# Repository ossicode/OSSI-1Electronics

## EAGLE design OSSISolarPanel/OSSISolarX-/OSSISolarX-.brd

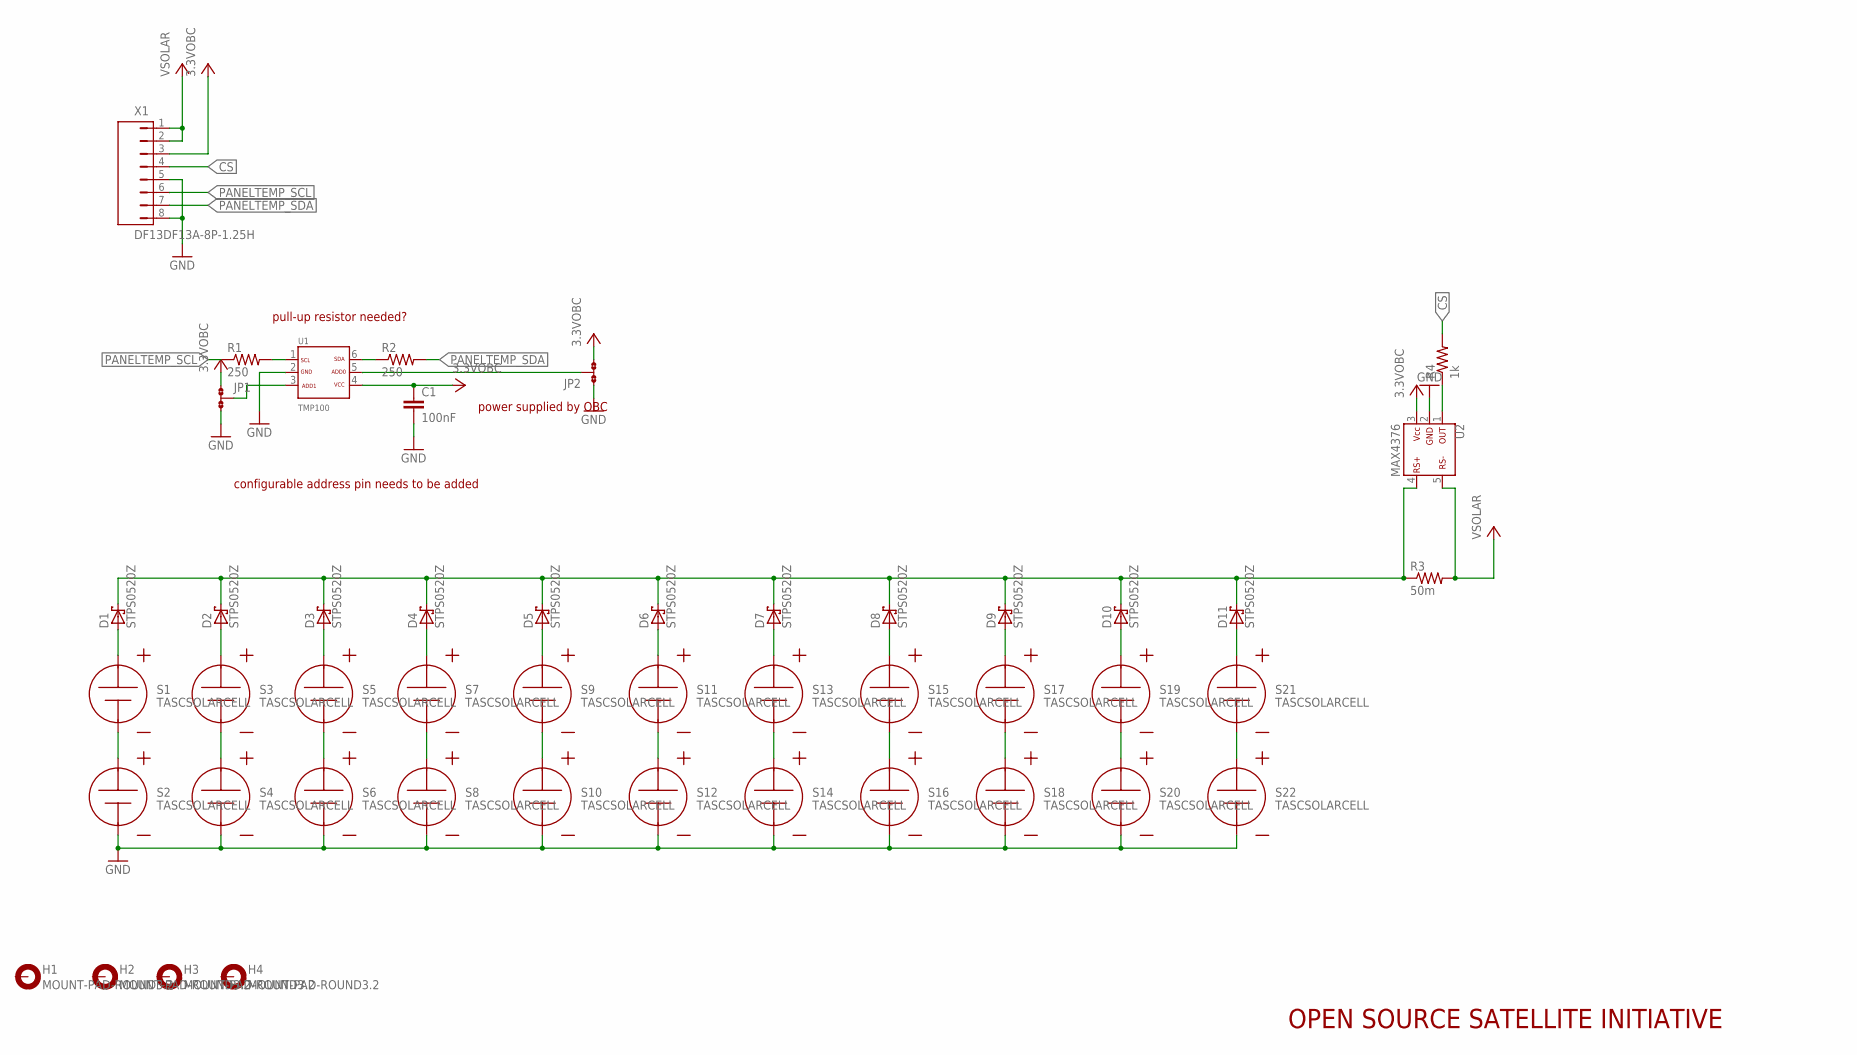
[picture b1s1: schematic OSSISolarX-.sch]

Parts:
C1: 100nF; C0603(1608)
D1, D2, D3, D4, D5, D6, D7, D8, D9, D10, D11: STPS0520Z; SOD-123
H1, H2, H3, H4: MOUNT-PAD-ROUND3.2; 3.2-PAD-ROUND
JP1, JP2: JP2; JP2SMD0603
R1, R2: 250; R0603(1608)
R3: 50m; WSL1206
R4: 1k; R0603(1608)
S1, S2, S3, S4, S5, S6, S7, S8, S9, S10, S11, S12, S13, S14, S15, S16, S17, S18, S19, S20, S21, S22: TASCSOLARCELL
U1: TMP100; SOT23-6DBV
U2: MAX4376; SOT23-5DBV
X1: DF13DF13A-8P-1.25H; DF13A-8P

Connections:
3.3VOBC: C1.1, JP1.1, JP2.3, U1.4, U2.3, X1.3
CS: R4.2, X1.4
GND: C1.2, JP1.3, JP2.1, S2.N, S4.N, S6.N, S8.N, S10.N, S12.N, S14.N, S16.N, S18.N, S20.N, S22.N, U1.2, U2.2, X1.5, X1.8
unnamed: S1.N, S2.P
unnamed: D1.A, S1.P
unnamed: S3.N, S4.P
unnamed: D2.A, S3.P
unnamed: S5.N, S6.P
unnamed: D3.A, S5.P
unnamed: S7.N, S8.P
unnamed: D4.A, S7.P
unnamed: S9.N, S10.P
unnamed: D5.A, S9.P
unnamed: S11.N, S12.P
unnamed: D6.A, S11.P
unnamed: S13.N, S14.P
unnamed: D7.A, S13.P
unnamed: S15.N, S16.P
unnamed: D8.A, S15.P
unnamed: S17.N, S18.P
unnamed: D9.A, S17.P
unnamed: S19.N, S20.P
unnamed: D10.A, S19.P
unnamed: S21.N, S22.P
unnamed: D11.A, S21.P
unnamed: R1.2, U1.1
unnamed: R2.1, U1.6
unnamed: D1.C, D2.C, D3.C, D4.C, D5.C, D6.C, D7.C, D8.C, D9.C, D10.C, D11.C, R3.P$1 (1), U2.4
unnamed: JP1.2, U1.3
unnamed: JP2.2, U1.5
unnamed: R4.1, U2.1
PANELTEMP_SCL: R1.1, X1.6
PANELTEMP_SDA: R2.2, X1.7
VSOLAR: R3.P$2 (2), U2.5, X1.1, X1.2

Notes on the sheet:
configurable address pin needs to be added
pull-up resistor needed?
power supplied by OBC
OPEN SOURCE SATELLITE INITIATIVE

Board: 2 copper layers, 47 parts (0 on the bottom side), 34 nets, no tracks yet.

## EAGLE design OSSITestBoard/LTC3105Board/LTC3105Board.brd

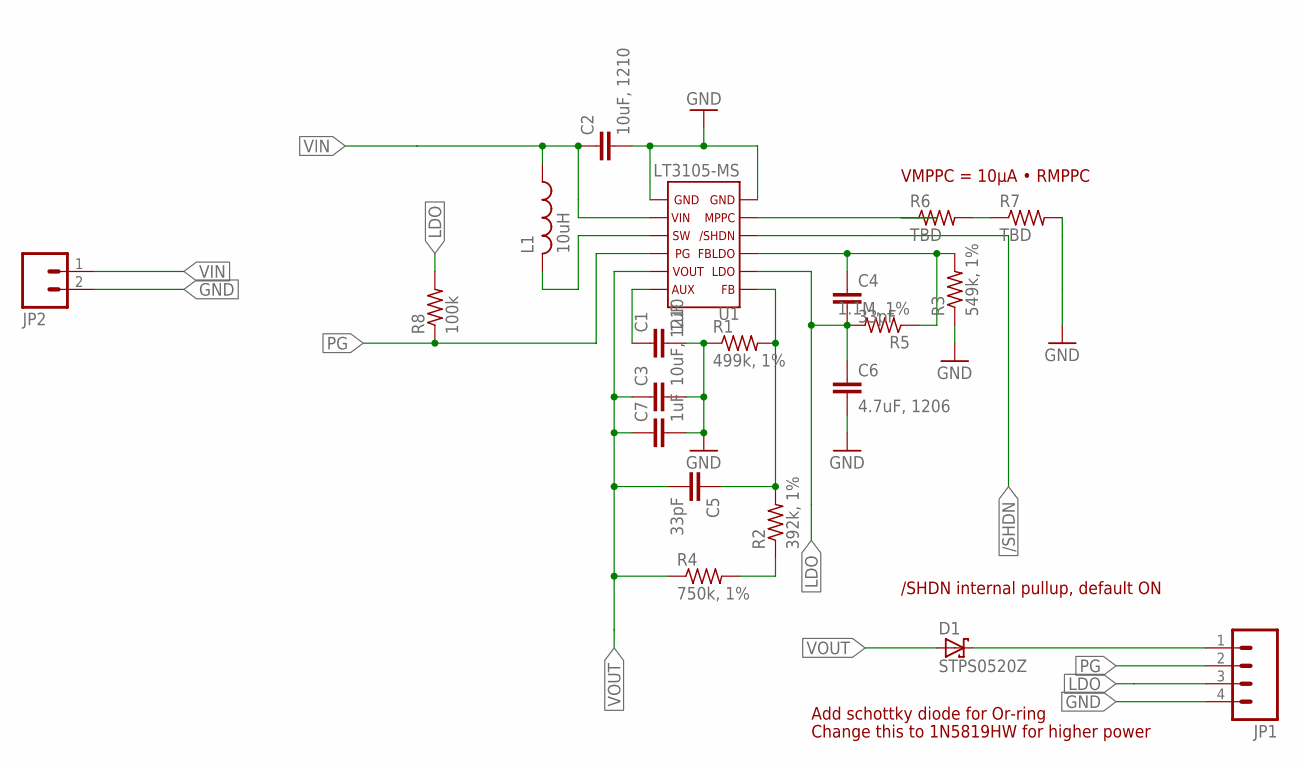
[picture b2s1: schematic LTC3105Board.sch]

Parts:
C1, C7: 1uF; C0603(1608)
C2, C3: 10uF, 1210; C1210-GCM32
C4, C5: 33pF; C0603(1608)
C6: 4.7uF, 1206; C1206-GCM31
D1: STPS0520Z; SOD-123
JP1: M04PTH; 1X04
JP2: M02PTH; 1X02
L1: 10uH; CDRH3D18
R1: 499k, 1%; R0603(1608)
R2: 392k, 1%; R0603(1608)
R3: 549k, 1%; R0603(1608)
R4: 750k, 1%; R0603(1608)
R5: 1.1M, 1%; R0603(1608)
R6, R7: TBD; R0603(1608)
R8: 100k; R0603(1608)
U1: LT3105-MS; MSOP-12-MS

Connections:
/SHDN: U1.4
GND: C1.2, C2.P$2 (2), C3.P$2 (2), C6.P$2 (2), C7.2, JP1.4, JP2.2, R1.1, R3.1, R7.2, U1.6, U1.7
LDO: C4.2, C6.P$1 (1), JP1.3, R5.2, R8.2, U1.2
unnamed: D1.C, JP1.1
unnamed: L1.P$2 (2), U1.9
unnamed: C1.1, U1.12
unnamed: C5.1, R1.2, R2.2, U1.1
unnamed: C4.1, R3.2, R5.1, U1.3
unnamed: R2.1, R4.2
unnamed: R6.1, U1.5
unnamed: R6.2, R7.1
PG: JP1.2, R8.1, U1.10
VIN: C2.P$1 (1), JP2.1, L1.P$1 (1), U1.8
VOUT: C3.P$1 (1), C5.2, C7.1, D1.A, R4.1, U1.11

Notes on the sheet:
VMPPC = 10µA • RMPPC
/SHDN internal pullup, default ON
Add schottky diode for Or-ring
Change this to 1N5819HW for higher power

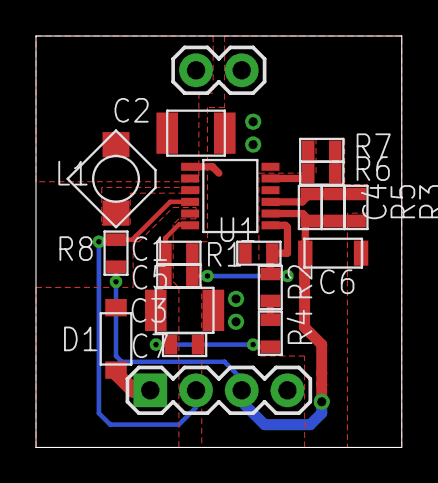
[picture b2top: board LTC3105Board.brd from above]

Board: 2 copper layers, 20.3 x 22.9 mm, 20 parts (0 on the bottom side), 13 nets.

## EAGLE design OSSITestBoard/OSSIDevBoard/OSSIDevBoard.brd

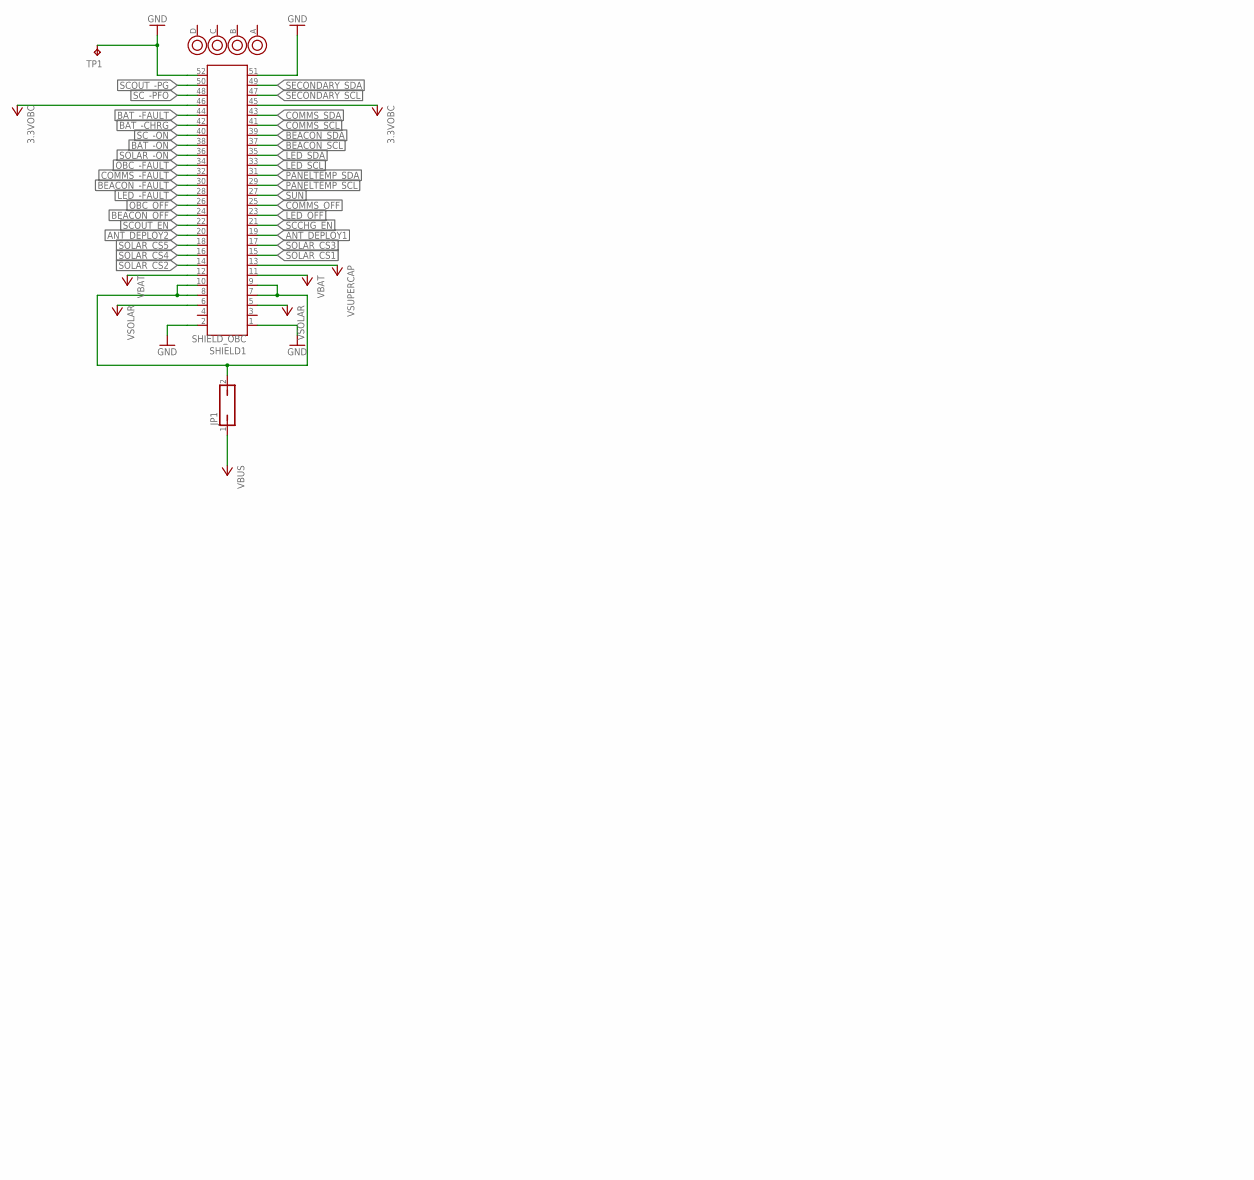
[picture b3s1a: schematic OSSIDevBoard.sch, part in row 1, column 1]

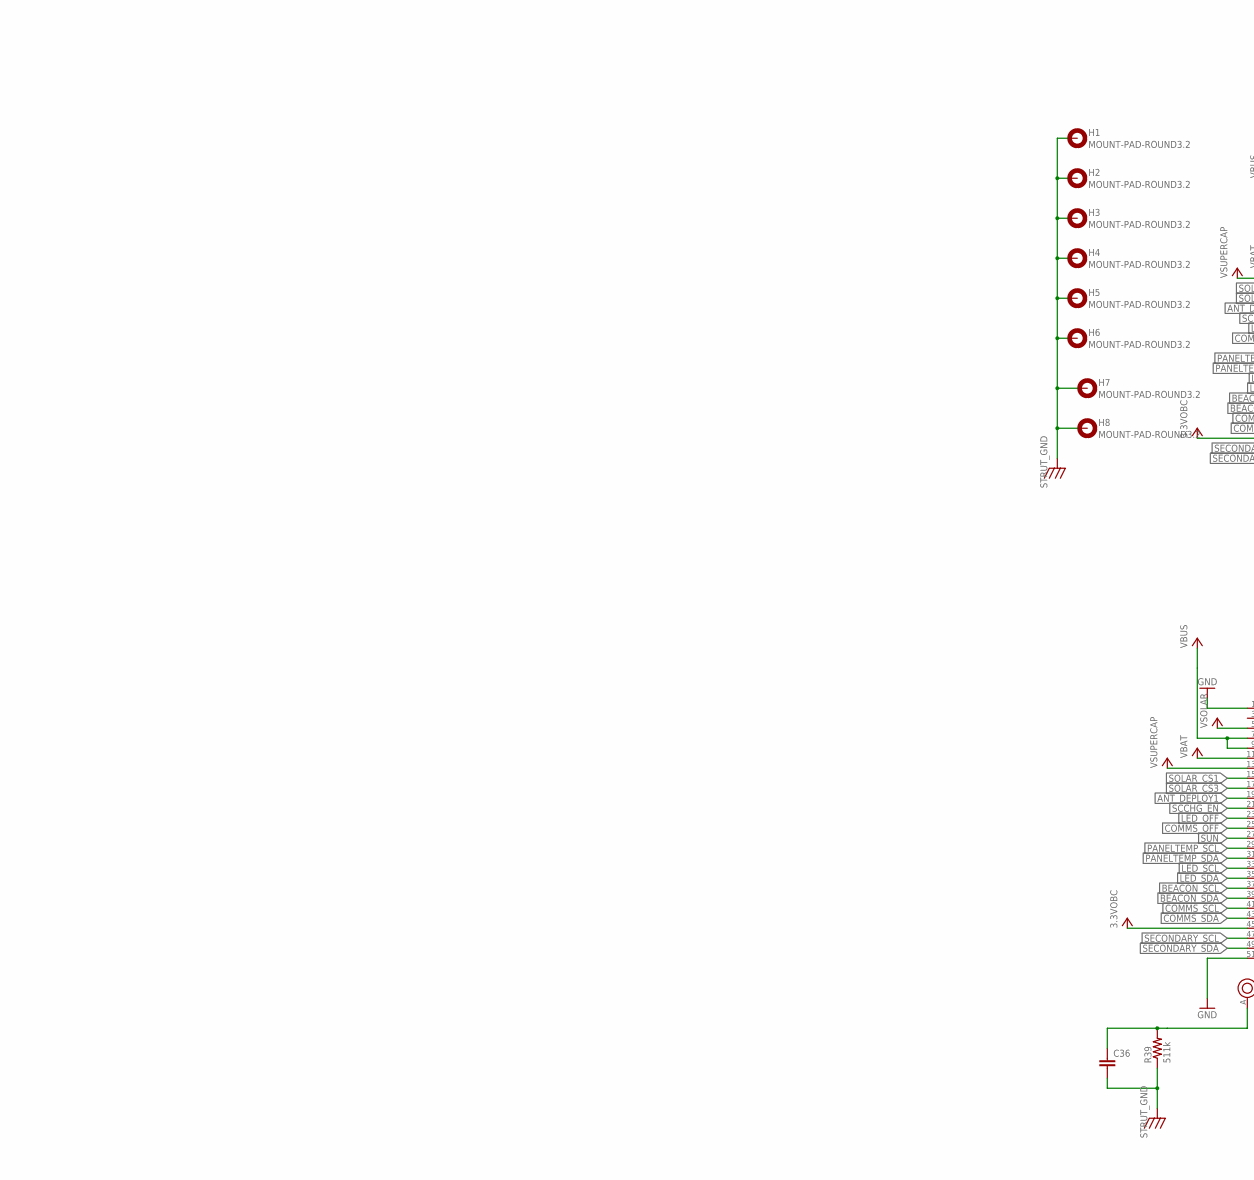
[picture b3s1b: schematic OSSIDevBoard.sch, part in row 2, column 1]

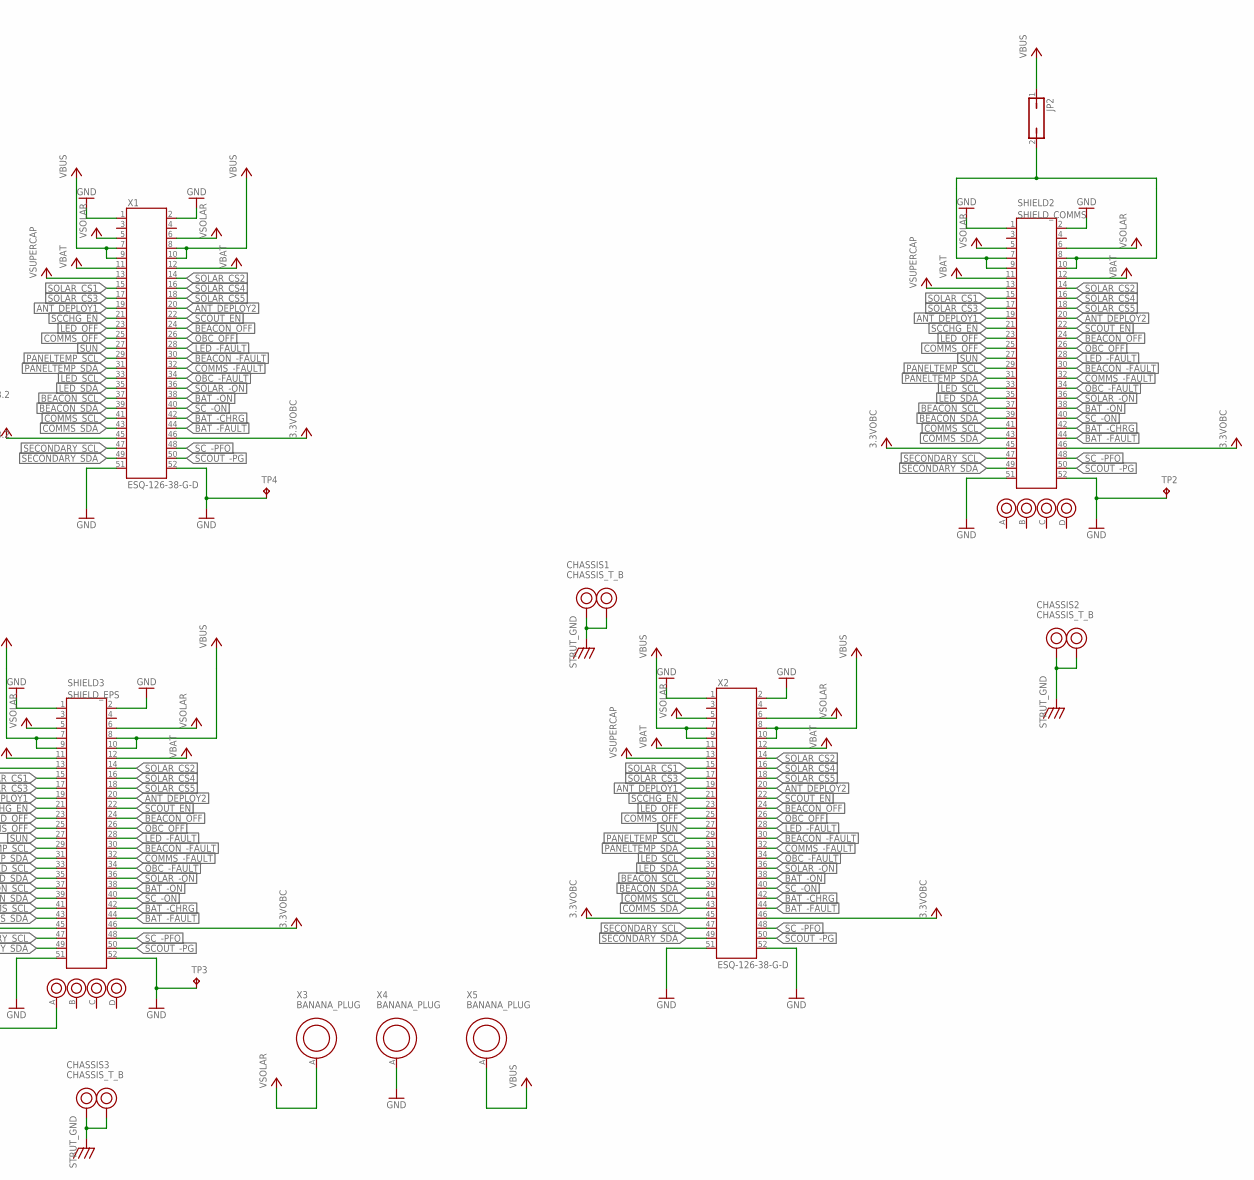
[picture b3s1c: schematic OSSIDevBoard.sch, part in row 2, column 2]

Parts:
C36: C0805(2012)
CHASSIS1, CHASSIS2, CHASSIS3: CHASSIS_T_B
H1, H2, H3, H4, H5, H6, H7, H8: MOUNT-PAD-ROUND3.2; 3.2-PAD-ROUND
JP1, JP2: JP1Q; JP1
R39: 511k; R0805(2012)
SHIELD1: SHIELD_OBC; OBC_SHIELD
SHIELD2: SHIELD_COMMS; COMMS_SHIELD
SHIELD3: SHIELD_EPS; EPS_SHIELD
TP1, TP2, TP3, TP4: TP; TP-13
X1, X2: ESQ-126-38-G-D; ESQ-126-XX-X-D
X3, X4, X5: BANANA_PLUG

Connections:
3.3VOBC: SHIELD1.45, SHIELD1.46, SHIELD2.45, SHIELD2.46, SHIELD3.45, SHIELD3.46, X1.45, X1.46, X2.45, X2.46
ANT_DEPLOY1: SHIELD1.19, SHIELD2.19, SHIELD3.19, X1.19, X2.19
ANT_DEPLOY2: SHIELD1.20, SHIELD2.20, SHIELD3.20, X1.20, X2.20
BAT_-CHRG: SHIELD1.42, SHIELD2.42, SHIELD3.42, X1.42, X2.42
BAT_-FAULT: SHIELD1.44, SHIELD2.44, SHIELD3.44, X1.44, X2.44
BAT_-ON: SHIELD1.38, SHIELD2.38, SHIELD3.38, X1.38, X2.38
BEACON_-FAULT: SHIELD1.30, SHIELD2.30, SHIELD3.30, X1.30, X2.30
BEACON_OFF: SHIELD1.24, SHIELD2.24, SHIELD3.24, X1.24, X2.24
BEACON_SCL: SHIELD1.37, SHIELD2.37, SHIELD3.37, X1.37, X2.37
BEACON_SDA: SHIELD1.39, SHIELD2.39, SHIELD3.39, X1.39, X2.39
COMMS_-FAULT: SHIELD1.32, SHIELD2.32, SHIELD3.32, X1.32, X2.32
COMMS_OFF: SHIELD1.25, SHIELD2.25, SHIELD3.25, X1.25, X2.25
COMMS_SCL: SHIELD1.41, SHIELD2.41, SHIELD3.41, X1.41, X2.41
COMMS_SDA: SHIELD1.43, SHIELD2.43, SHIELD3.43, X1.43, X2.43
GND: SHIELD1.1, SHIELD1.2, SHIELD1.51, SHIELD1.52, SHIELD2.1, SHIELD2.2, SHIELD2.51, SHIELD2.52, SHIELD3.1, SHIELD3.2, SHIELD3.51, SHIELD3.52, TP1.TP, TP2.TP, TP3.TP, TP4.TP, X1.1, X1.2, X1.51, X1.52, X2.1, X2.2, X2.51, X2.52, X4.A
LED_-FAULT: SHIELD1.28, SHIELD2.28, SHIELD3.28, X1.28, X2.28
LED_OFF: SHIELD1.23, SHIELD2.23, SHIELD3.23, X1.23, X2.23
LED_SCL: SHIELD1.33, SHIELD2.33, SHIELD3.33, X1.33, X2.33
LED_SDA: SHIELD1.35, SHIELD2.35, SHIELD3.35, X1.35, X2.35
unnamed: JP1.2, SHIELD1.7, SHIELD1.8, SHIELD1.9, SHIELD1.10
unnamed: JP2.2, SHIELD2.7, SHIELD2.8, SHIELD2.9, SHIELD2.10
OBC_-FAULT: SHIELD1.34, SHIELD2.34, SHIELD3.34, X1.34, X2.34
OBC_OFF: SHIELD1.26, SHIELD2.26, SHIELD3.26, X1.26, X2.26
PANELTEMP_SCL: SHIELD1.29, SHIELD2.29, SHIELD3.29, X1.29, X2.29
PANELTEMP_SDA: SHIELD1.31, SHIELD2.31, SHIELD3.31, X1.31, X2.31
SCCHG_EN: SHIELD1.21, SHIELD2.21, SHIELD3.21, X1.21, X2.21
SCOUT_-PG: SHIELD1.50, SHIELD2.50, SHIELD3.50, X1.50, X2.50
SCOUT_EN: SHIELD1.22, SHIELD2.22, SHIELD3.22, X1.22, X2.22
SC_-ON: SHIELD1.40, SHIELD2.40, SHIELD3.40, X1.40, X2.40
SC_-PFO: SHIELD1.48, SHIELD2.48, SHIELD3.48, X1.48, X2.48
SECONDARY_SCL: SHIELD1.47, SHIELD2.47, SHIELD3.47, X1.47, X2.47
SECONDARY_SDA: SHIELD1.49, SHIELD2.49, SHIELD3.49, X1.49, X2.49
SOLAR_-ON: SHIELD1.36, SHIELD2.36, SHIELD3.36, X1.36, X2.36
SOLAR_CS1: SHIELD1.15, SHIELD2.15, SHIELD3.15, X1.15, X2.15
SOLAR_CS2: SHIELD1.14, SHIELD2.14, SHIELD3.14, X1.14, X2.14
SOLAR_CS3: SHIELD1.17, SHIELD2.17, SHIELD3.17, X1.17, X2.17
SOLAR_CS4: SHIELD1.16, SHIELD2.16, SHIELD3.16, X1.16, X2.16
SOLAR_CS5: SHIELD1.18, SHIELD2.18, SHIELD3.18, X1.18, X2.18
STRUT_GND: C36.2, CHASSIS1.A, CHASSIS1.B, CHASSIS2.A, CHASSIS2.B, CHASSIS3.A, CHASSIS3.B, H1.B3,2, H2.B3,2, H3.B3,2, H4.B3,2, H5.B3,2, H6.B3,2, H7.B3,2, H8.B3,2, R39.1
STRUT_GND1: C36.1, R39.2, SHIELD3.A
SUN: SHIELD1.27, SHIELD2.27, SHIELD3.27, X1.27, X2.27
VBAT: SHIELD1.11, SHIELD1.12, SHIELD2.11, SHIELD2.12, SHIELD3.11, SHIELD3.12, X1.11, X1.12, X2.11, X2.12
VBUS: JP1.1, JP2.1, SHIELD3.7, SHIELD3.8, SHIELD3.9, SHIELD3.10, X1.7, X1.8, X1.9, X1.10, X2.7, X2.8, X2.9, X2.10, X5.A
VSOLAR: SHIELD1.5, SHIELD1.6, SHIELD2.5, SHIELD2.6, SHIELD3.5, SHIELD3.6, X1.5, X1.6, X2.5, X2.6, X3.A
VSUPERCAP: SHIELD1.13, SHIELD2.13, SHIELD3.13, X1.13, X2.13

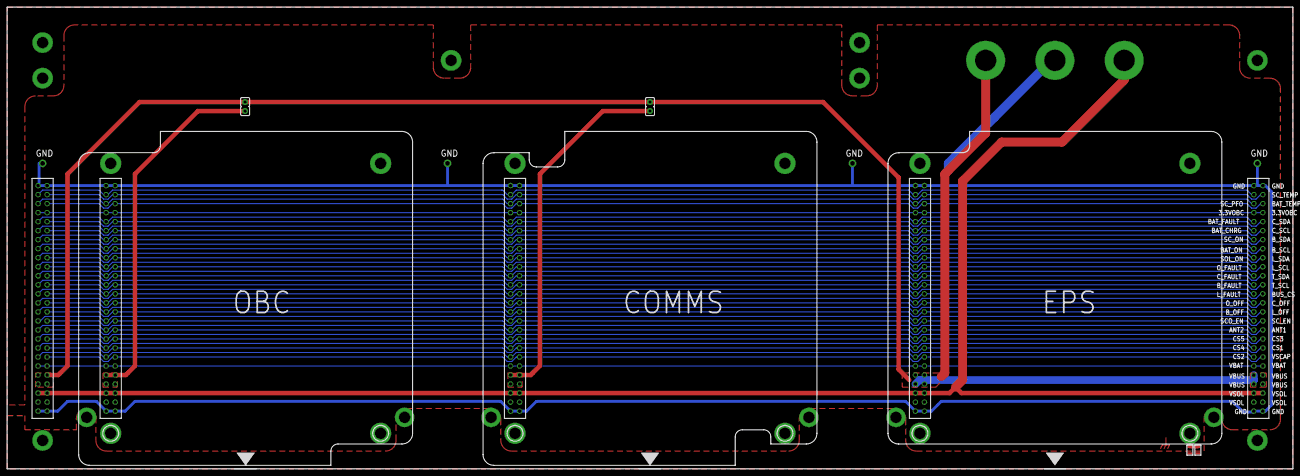
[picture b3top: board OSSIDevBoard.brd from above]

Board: 2 copper layers, 362.0 x 130.0 mm, 27 parts (0 on the bottom side), 45 nets.

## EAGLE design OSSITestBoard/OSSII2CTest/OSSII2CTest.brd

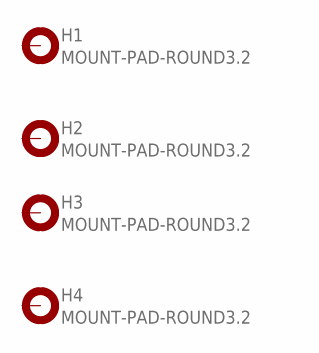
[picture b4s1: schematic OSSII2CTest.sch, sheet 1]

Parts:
H1, H2, H3, H4: MOUNT-PAD-ROUND3.2; 3.2-PAD-ROUND

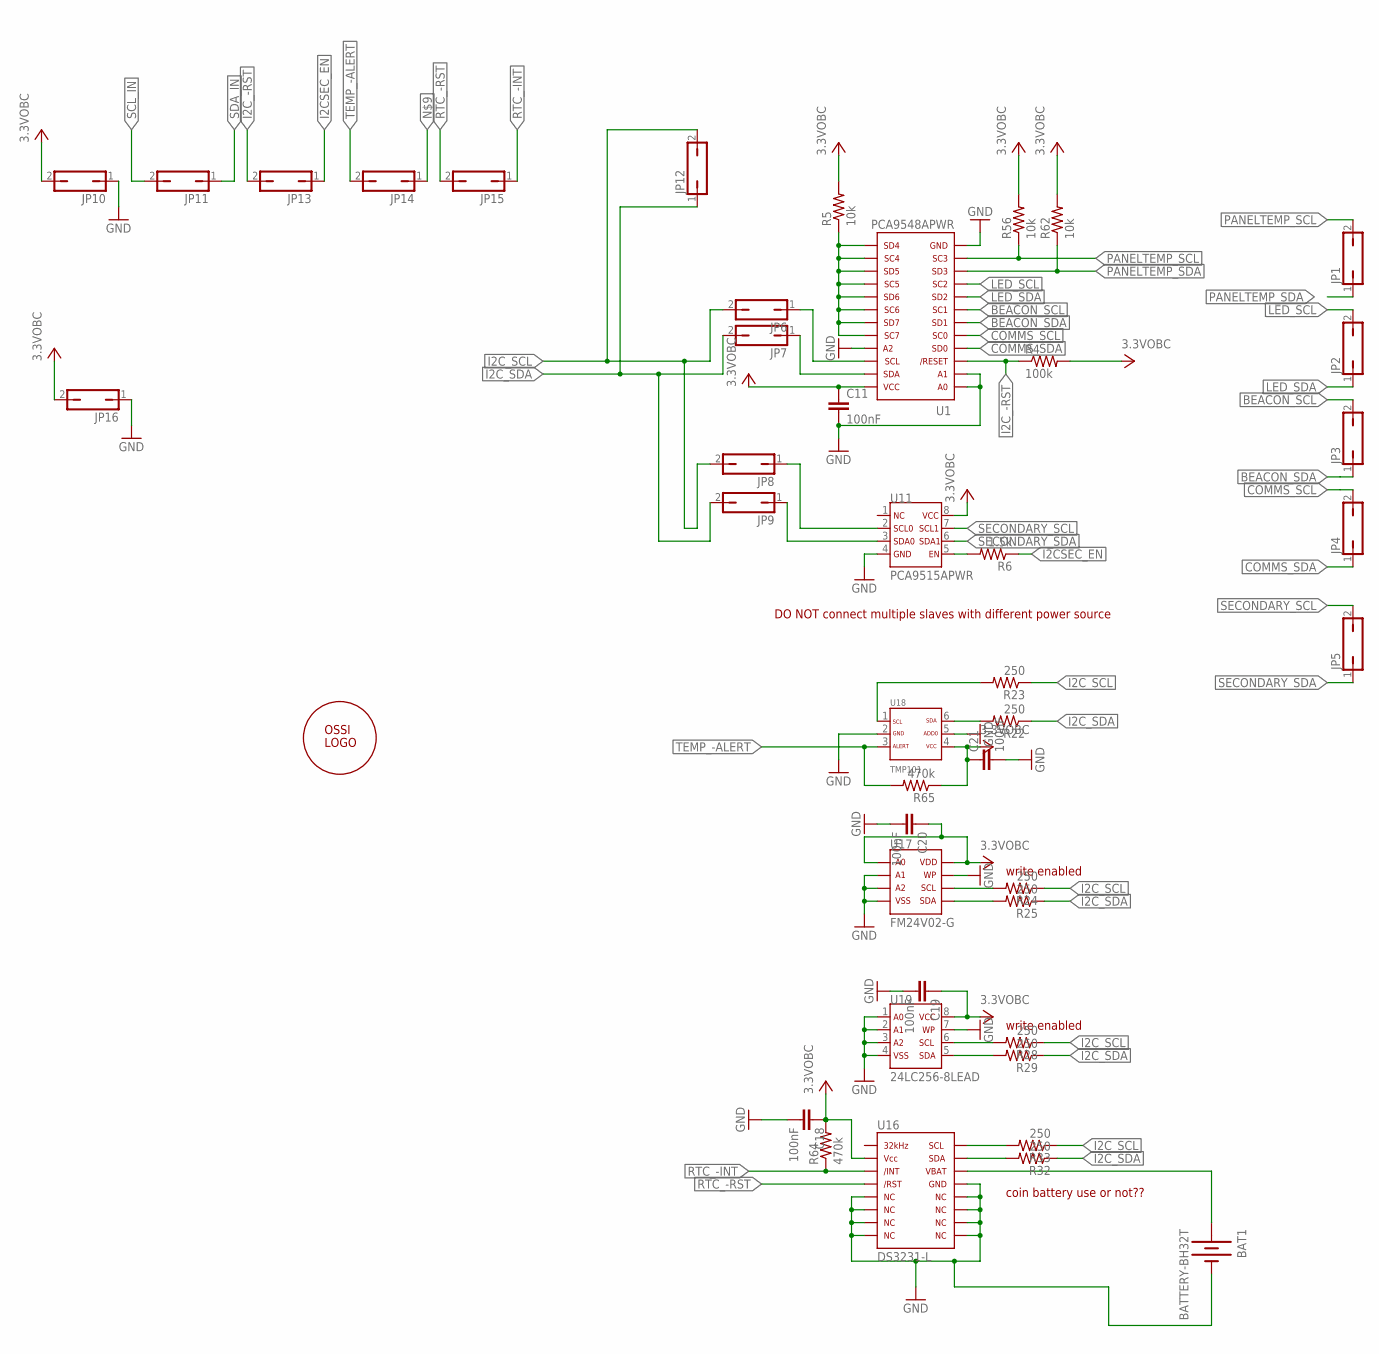
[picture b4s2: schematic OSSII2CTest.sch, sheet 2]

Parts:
BAT1: BATTERY-BH32T; BH32T-C-G
C11, C18, C19, C20, C21: 100nF; C0603(1608)
JP1, JP2, JP3, JP4, JP5, JP6, JP7, JP8, JP9, JP10, JP11, JP12, JP13, JP14, JP15, JP16: JP1Q; JP1
R4: 100k; R0603(1608)
R5, R56, R62: 10k; R0603(1608)
R6: 1.5k; R0603(1608)
R22, R23, R24, R25, R28, R29, R32, R33: 250; R0603(1608)
R64, R65: 470k; R0603(1608)
U1: PCA9548APWR; TSSOP-24-PW
U11: PCA9515APWR; TSSOP-8
U16: DS3231-L; SO16L
U17: FM24V02-G; SO8
U18: TMP101; SOT23-6DBV
U19: 24LC256-8LEAD; SO08-208
U$1: OSSITAG; OSSISCIENCEISFANTASY

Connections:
3.3VOBC: C11.1, C18.1, C19.1, C20.1, C21.1, JP10.2, JP16.2, R4.2, R5.2, R56.2, R62.2, R64.2, R65.1, U1.24, U11.8, U16.2, U17.1 (A0), U17.8 (VDD), U18.4, U19.8; also elsewhere on the board
BEACON_SCL: JP3.2, U1.7
BEACON_SDA: JP3.1, U1.6
COMMS_SCL: JP4.2, U1.5
COMMS_SDA: JP4.1, U1.4
GND: BAT1.N (-), C11.2, C18.2, C19.2, C20.2, C21.2, JP10.1, JP16.1, U1.1, U1.2, U1.12, U1.21, U11.4, U16.5, U16.6, U16.7, U16.8, U16.9, U16.10, U16.11, U16.12, U16.13, U17.2 (A1), U17.3 (A2), U17.4 (VSS), U17.7 (WP), U18.2, U18.5, U19.1, U19.2, U19.3, U19.4, U19.7
I2CSEC_EN: JP13.1, R6.1
I2C_-RST: JP13.2, R4.1, U1.3
I2C_SCL: JP6.2, JP8.2, JP12.2, R23.1, R24.1, R28.1, R33.1; also elsewhere on the board
I2C_SDA: JP7.2, JP9.2, JP12.1, R22.1, R25.1, R29.1, R32.1; also elsewhere on the board
LED_SCL: JP2.2, U1.9
LED_SDA: JP2.1, U1.8
unnamed: JP6.1, U1.22
unnamed: JP7.1, U1.23
unnamed: JP8.1, U11.2
unnamed: JP9.1, U11.3
unnamed: R32.2, U16.15
unnamed: R33.2, U16.16
unnamed: R5.1, U1.13, U1.14, U1.15, U1.16, U1.17, U1.18, U1.19, U1.20
unnamed: R29.2, U19.5
unnamed: R28.2, U19.6
unnamed: R25.2, U17.5 (SDA)
unnamed: R24.2, U17.6 (SCL)
unnamed: R22.2, U18.6
unnamed: R23.2, U18.1
unnamed: R6.2, U11.5
unnamed: BAT1.P (+), U16.14
PANELTEMP_SCL: JP1.2, R56.1, U1.11
PANELTEMP_SDA: JP1.1, R62.1, U1.10
RTC_-INT: JP15.1, R64.1, U16.3
RTC_-RST: JP15.2, U16.4
SCL_IN: JP11.2; also elsewhere on the board
SDA_IN: JP11.1; also elsewhere on the board
SECONDARY_SCL: JP5.2, U11.7
SECONDARY_SDA: JP5.1, U11.6
TEMP_-ALERT: JP14.2, R65.2, U18.3

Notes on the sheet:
DO NOT connect multiple slaves with different power source
coin battery use or not??
write enabled

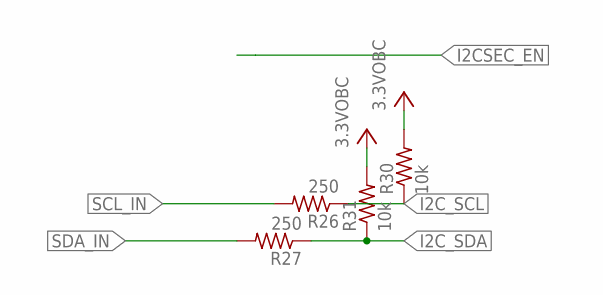
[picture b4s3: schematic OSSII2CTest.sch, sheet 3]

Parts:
R26, R27: 250; R0603(1608)
R30, R31: 10k; R0603(1608)

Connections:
3.3VOBC: R30.2, R31.2; also elsewhere on the board
I2C_SCL: R26.1, R30.1; also elsewhere on the board
I2C_SDA: R27.1, R31.1; also elsewhere on the board
SCL_IN: R26.2; also elsewhere on the board
SDA_IN: R27.2; also elsewhere on the board

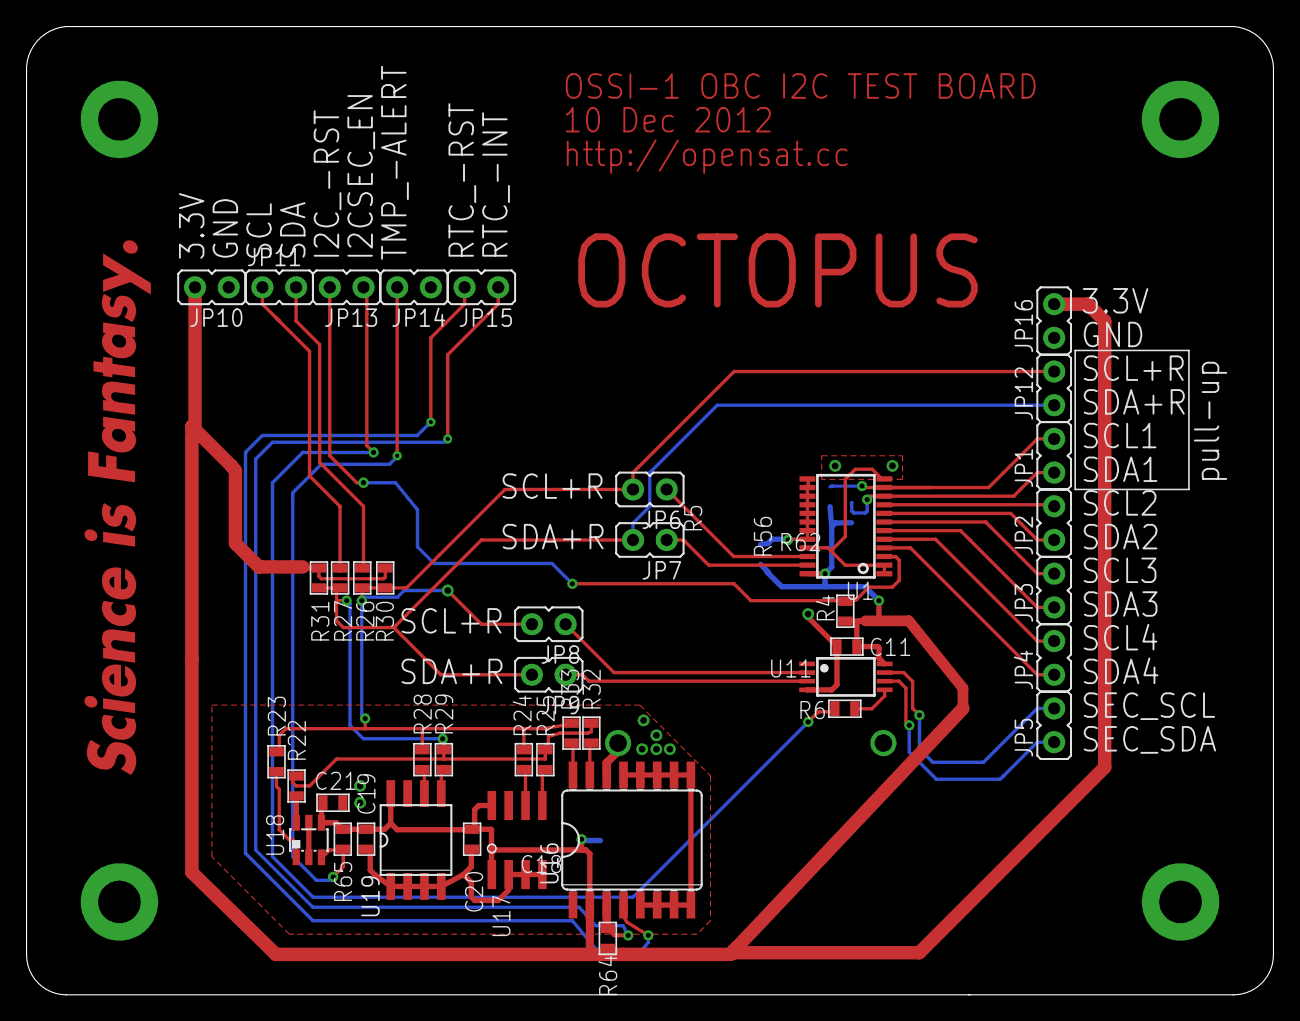
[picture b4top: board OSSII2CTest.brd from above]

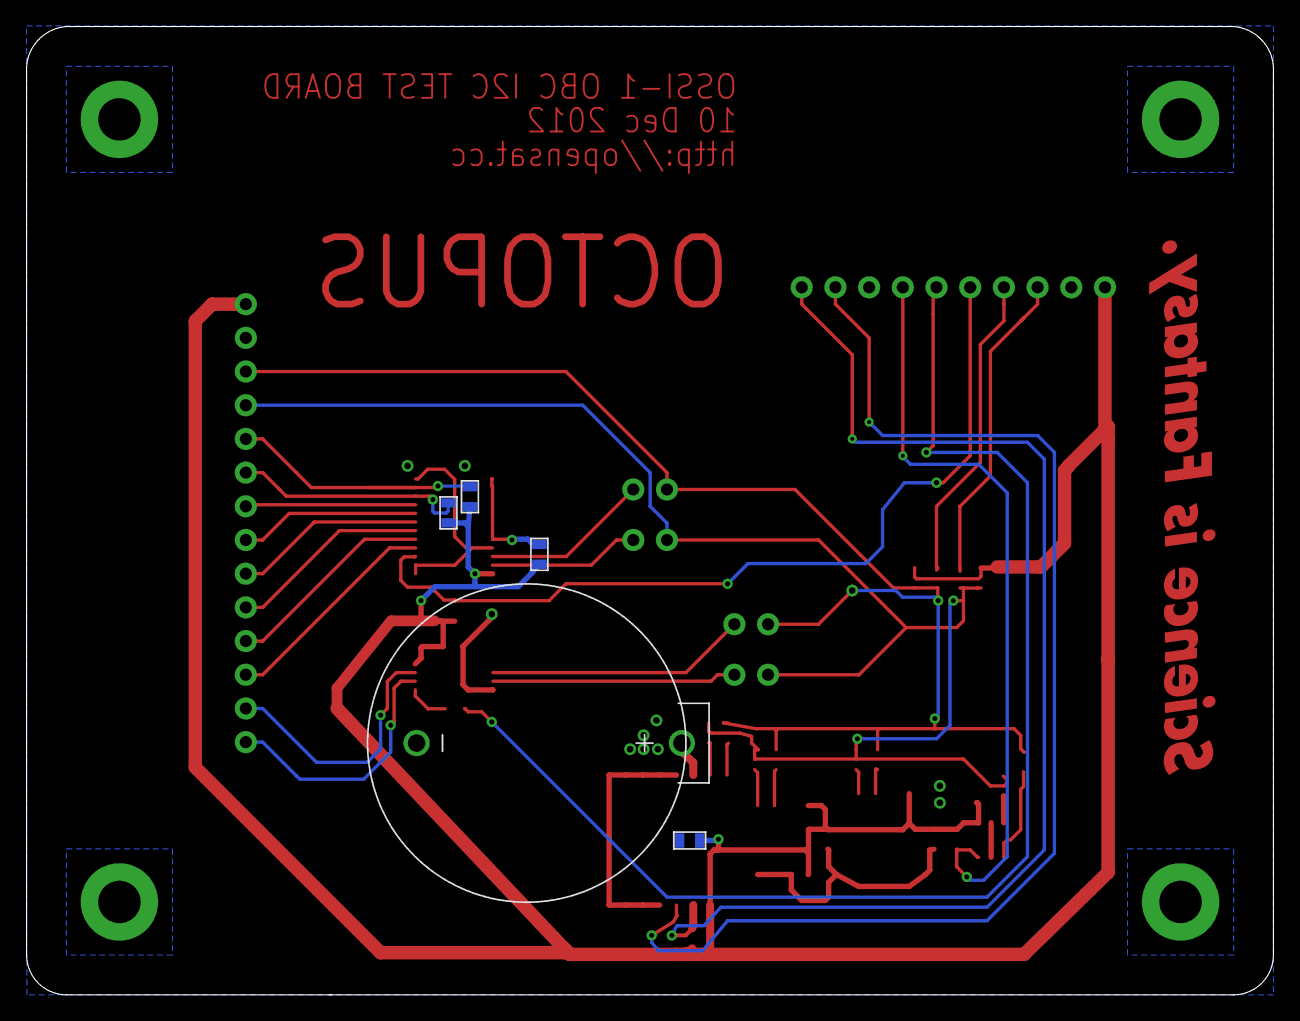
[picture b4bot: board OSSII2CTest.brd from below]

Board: 2 copper layers, 94.0 x 73.0 mm, 52 parts (5 on the bottom side), 36 nets.

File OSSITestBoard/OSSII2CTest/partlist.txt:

Partlist

Exported from OSSII2CTest.sch at 2012-12-10 ¿ÀÈÄ 5:48:37

EAGLE Version 6.1.0 Copyright (c) 1988-2012 CadSoft

Assembly variant: 

Part     Value              Device             Package       Library  Sheet

BAT1     BATTERY-BH32T      BATTERY-BH32T      BH32T-C-G     OSSI     2
C11      100nF              C0603(1608)        C0603(1608)   OSSI     2
C18      100nF              C0603(1608)        C0603(1608)   OSSI     2
C19      100nF              C0603(1608)        C0603(1608)   OSSI     2
C20      100nF              C0603(1608)        C0603(1608)   OSSI     2
C21      100nF              C0603(1608)        C0603(1608)   OSSI     2
H1       MOUNT-PAD-ROUND3.2 MOUNT-PAD-ROUND3.2 3.2-PAD-ROUND OSSI     1
H2       MOUNT-PAD-ROUND3.2 MOUNT-PAD-ROUND3.2 3.2-PAD-ROUND OSSI     1
H3       MOUNT-PAD-ROUND3.2 MOUNT-PAD-ROUND3.2 3.2-PAD-ROUND OSSI     1
H4       MOUNT-PAD-ROUND3.2 MOUNT-PAD-ROUND3.2 3.2-PAD-ROUND OSSI     1
JP1                         JP1Q               JP1           OSSI     2
JP2                         JP1Q               JP1           OSSI     2
JP3                         JP1Q               JP1           OSSI     2
JP4                         JP1Q               JP1           OSSI     2
JP5                         JP1Q               JP1           OSSI     2
JP6                         JP1Q               JP1           OSSI     2
JP7                         JP1Q               JP1           OSSI     2
JP8                         JP1Q               JP1           OSSI     2
JP9                         JP1Q               JP1           OSSI     2
JP10                        JP1Q               JP1           OSSI     2
JP11                        JP1Q               JP1           OSSI     2
JP12                        JP1Q               JP1           OSSI     2
JP13                        JP1Q               JP1           OSSI     2
JP14                        JP1Q               JP1           OSSI     2
JP15                        JP1Q               JP1           OSSI     2
JP16                        JP1Q               JP1           OSSI     2
R4       100k               R0603(1608)        R0603(1608)   OSSI     2
R5       10k                R0603(1608)        R0603(1608)   OSSI     2
R6       1.5k               R0603(1608)        R0603(1608)   OSSI     2
R22      250                R0603(1608)        R0603(1608)   OSSI     2
R23      250                R0603(1608)        R0603(1608)   OSSI     2
R24      250                R0603(1608)        R0603(1608)   OSSI     2
R25      250                R0603(1608)        R0603(1608)   OSSI     2
R26      250                R0603(1608)        R0603(1608)   OSSI     3
R27      250                R0603(1608)        R0603(1608)   OSSI     3
R28      250                R0603(1608)        R0603(1608)   OSSI     2
R29      250                R0603(1608)        R0603(1608)   OSSI     2
R30      10k                R0603(1608)        R0603(1608)   OSSI     3
R31      10k                R0603(1608)        R0603(1608)   OSSI     3
R32      250                R0603(1608)        R0603(1608)   OSSI     2
R33      250                R0603(1608)        R0603(1608)   OSSI     2
R56      10k                R0603(1608)        R0603(1608)   OSSI     2
R62      10k                R0603(1608)        R0603(1608)   OSSI     2
R64      470k               R0603(1608)        R0603(1608)   OSSI     2
R65      470k               R0603(1608)        R0603(1608)   OSSI     2
U1       PCA9548APWR        PCA9548APWR        TSSOP-24-PW   OSSI     2
U11      PCA9515APWR        PCA9515APWR        TSSOP-8       OSSI     2
U16      DS3231-L           DS3231-L           SO16L         OSSI     2
U17      FM24V02-G          FM24V02-G          SO8           OSSI     2
U18      TMP101             TMP101             SOT23-6DBV    OSSI     2
U19      24LC256-8LEAD      24LC256-8LEAD      SO08-208      OSSI     2
